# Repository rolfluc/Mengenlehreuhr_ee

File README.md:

# Mengenlehreuhr_ee
Project housing the electrical side of the Mengenlehreuhr project. Meant to be paired with the SW results.

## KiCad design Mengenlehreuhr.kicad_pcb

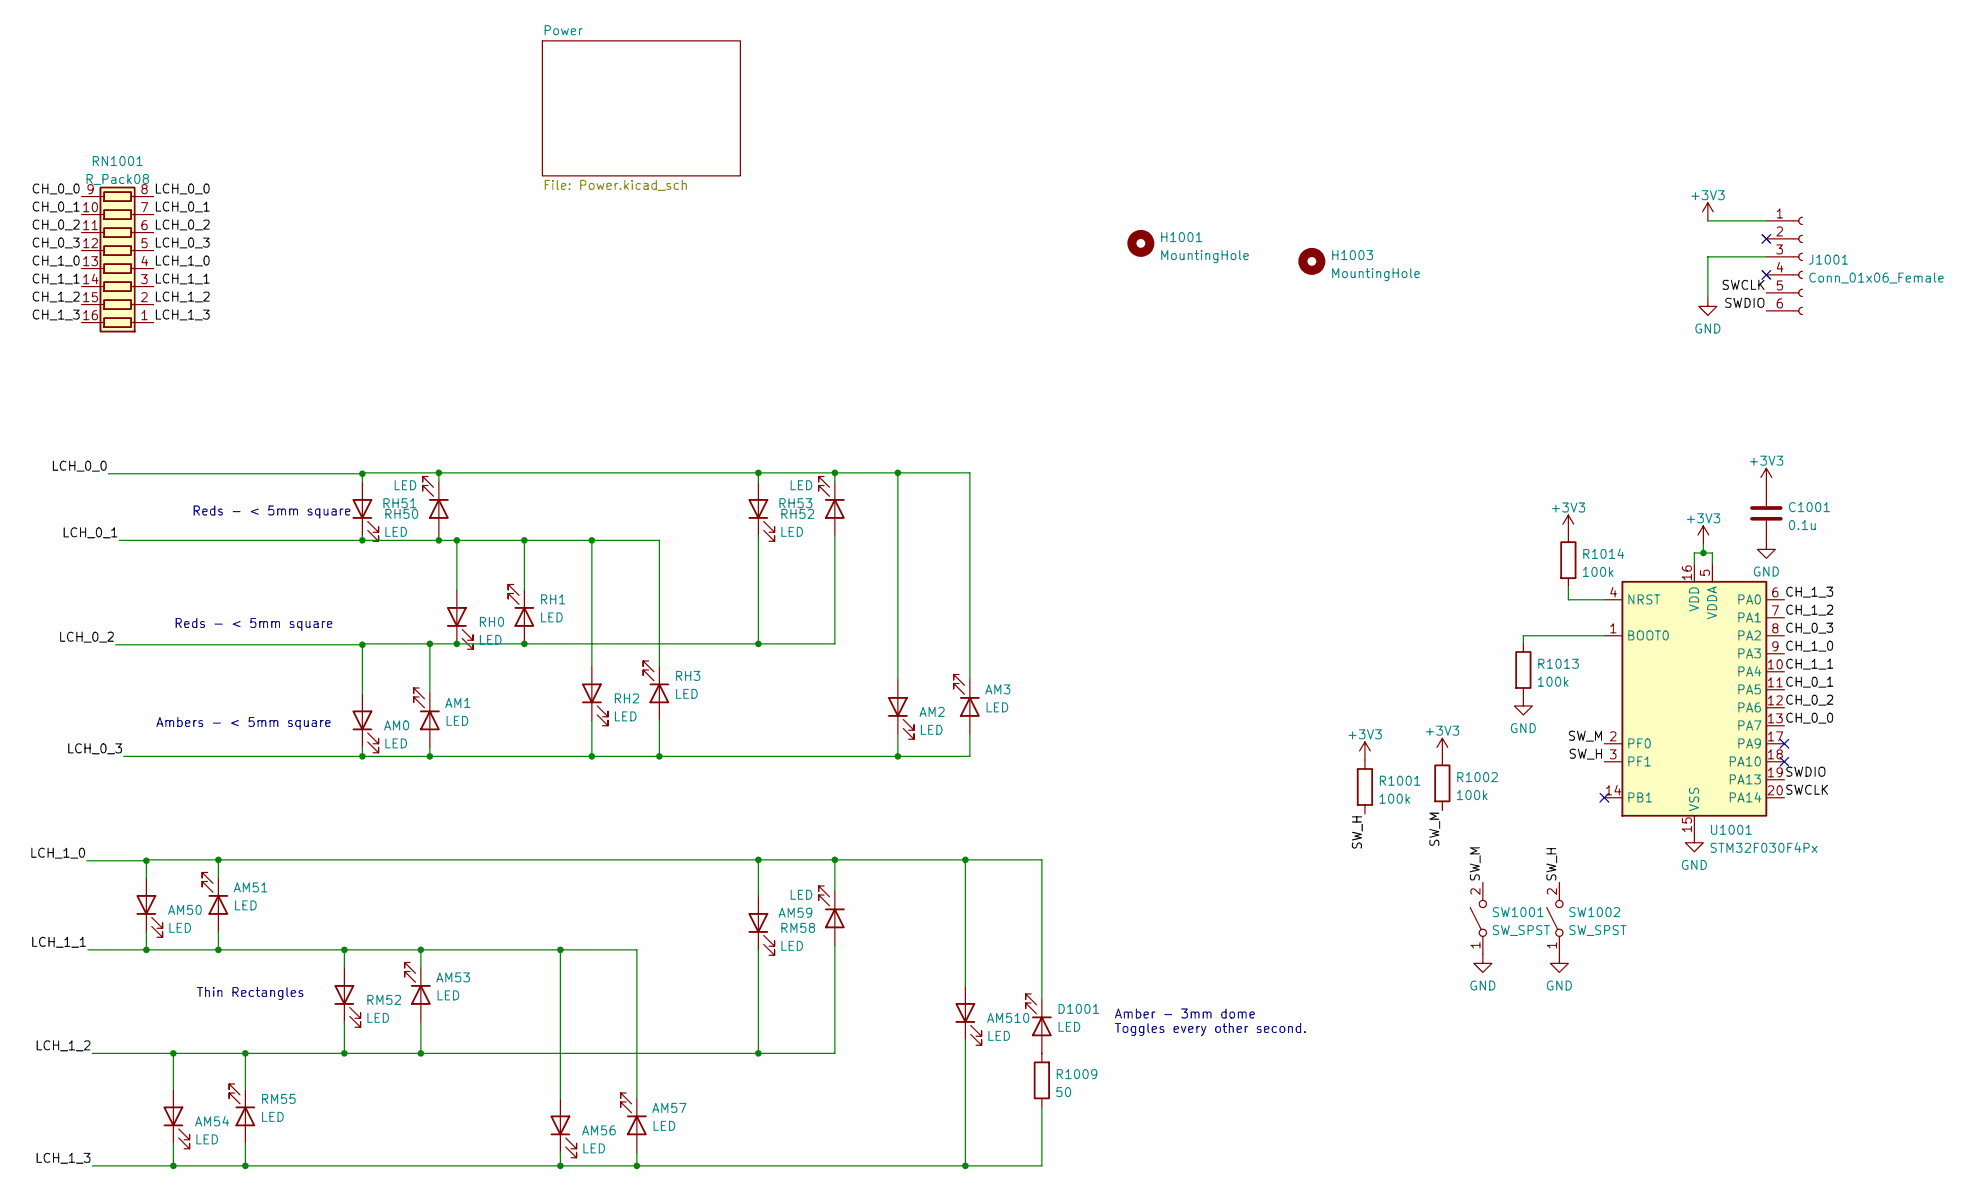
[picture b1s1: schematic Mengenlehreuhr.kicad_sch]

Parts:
AM0, AM1, AM2, AM3: LED; LED_1206_3216Metric
AM50, AM51, AM53, AM54, AM56, AM57, AM59, AM510: LED; LED_0603_1608Metric
C1001: 0.1u; C_0402_1005Metric
D1001: LED; LED_D3.0mm
H1001, H1003: MountingHole; MountingHole_3.2mm_M3
J1001: Conn_01x06_Female; Tag-Connect_TC2030-IDC-NL_2x03_P1.27mm_Vertical
R1001, R1002: 100k; R_0402_1005Metric_Pad0.72x0.64mm_HandSolder
R1009: 50; R_0402_1005Metric
R1013, R1014: 100k; R_0402_1005Metric
RH0, RH1, RH2, RH3, RH50, RH51, RH52, RH53: LED; LED_1206_3216Metric
RM52, RM55, RM58: LED; LED_0603_1608Metric
RN1001: R_Pack08; SOIC-16_3.9x9.9mm_P1.27mm
SW1001, SW1002: SW_SPST; SW_SPST_TL3305A
U1001: STM32F030F4Px; TSSOP-20_4.4x6.5mm_P0.65mm

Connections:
+3V3: C1001.1, J1001.1, R1001.1, R1002.1, R1014.1, U1001.5 (VDDA), U1001.16 (VDD); also elsewhere on the board
/CH_0_0: RN1001.9 (R8.2), U1001.13 (PA7)
/CH_0_1: RN1001.10 (R7.2), U1001.11 (PA5)
/CH_0_2: RN1001.11 (R6.2), U1001.12 (PA6)
/CH_0_3: RN1001.12 (R5.2), U1001.8 (PA2)
/CH_1_0: RN1001.13 (R4.2), U1001.9 (PA3)
/CH_1_1: RN1001.14 (R3.2), U1001.10 (PA4)
/CH_1_2: RN1001.15 (R2.2), U1001.7 (PA1)
/CH_1_3: RN1001.16 (R1.2), U1001.6 (PA0)
/LCH_0_0: AM2.2 (A), AM3.1 (K), RH50.2 (A), RH51.1 (K), RH52.2 (A), RH53.1 (K), RN1001.8 (R8.1)
/LCH_0_1: RH0.2 (A), RH1.1 (K), RH2.2 (A), RH3.1 (K), RH50.1 (K), RH51.2 (A), RN1001.7 (R7.1)
/LCH_0_2: AM0.2 (A), AM1.1 (K), RH0.1 (K), RH1.2 (A), RH52.1 (K), RH53.2 (A), RN1001.6 (R6.1)
/LCH_0_3: AM0.1 (K), AM1.2 (A), AM2.1 (K), AM3.2 (A), RH2.1 (K), RH3.2 (A), RN1001.5 (R5.1)
/LCH_1_0: AM50.2 (A), AM51.1 (K), AM59.1 (K), AM510.2 (A), D1001.1 (K), RM58.2 (A), RN1001.4 (R4.1)
/LCH_1_1: AM50.1 (K), AM51.2 (A), AM53.1 (K), AM56.2 (A), AM57.1 (K), RM52.2 (A), RN1001.3 (R3.1)
/LCH_1_2: AM53.2 (A), AM54.2 (A), AM59.2 (A), RM52.1 (K), RM55.1 (K), RM58.1 (K), RN1001.2 (R2.1)
/LCH_1_3: AM54.1 (K), AM56.1 (K), AM57.2 (A), AM510.1 (K), R1009.1, RM55.2 (A), RN1001.1 (R1.1)
/SWCLK: J1001.5, U1001.20 (PA14)
/SWDIO: J1001.6, U1001.19 (PA13)
/SW_H: R1001.2, SW1002.2 (B), U1001.3 (PF1)
/SW_M: R1002.2, SW1001.2 (B), U1001.2 (PF0)
GND: C1001.2, J1001.3, R1013.2, SW1001.1 (A), SW1002.1 (A), U1001.15 (VSS); also elsewhere on the board
unnamed: D1001.2 (A), R1009.2
unnamed: R1013.1, U1001.1 (BOOT0)
unnamed: R1014.2, U1001.4 (NRST)

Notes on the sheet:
Ambers - < 5mm square
Thin Rectangles
Amber - 3mm dome Toggles every other second.
Reds - < 5mm square

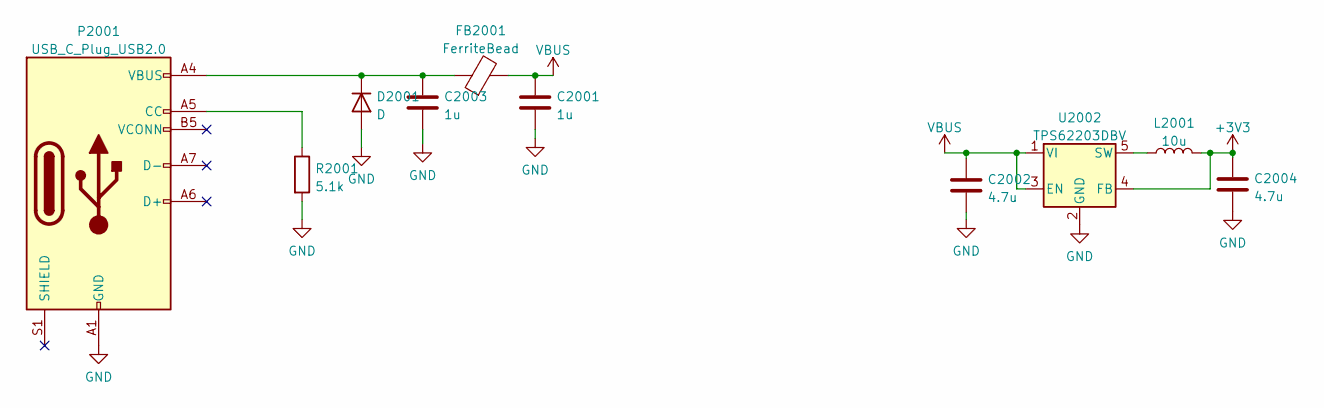
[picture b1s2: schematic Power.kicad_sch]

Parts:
C2001, C2003: 1u; C_0402_1005Metric
C2002, C2004: 4.7u; C_0603_1608Metric
D2001: D; D_0805_2012Metric_Pad1.15x1.40mm_HandSolder
FB2001: FerriteBead; R_0402_1005Metric_Pad0.72x0.64mm_HandSolder
L2001: 10u; L_1206_3216Metric
P2001: USB_C_Plug_USB2.0; USB_C_Receptacle_GCT_USB4085
R2001: 5.1k; R_0402_1005Metric
U2002: TPS62203DBV; SOT-23-5

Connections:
+3V3: C2004.1, L2001.2, U2002.4 (FB); also elsewhere on the board
GND: C2001.2, C2002.2, C2003.2, C2004.2, D2001.2 (A), P2001.A1 (GND), P2001.A12 (GND), P2001.B1 (GND), P2001.B12 (GND), R2001.2, U2002.2 (GND); also elsewhere on the board
unnamed 22: C2003.1, D2001.1 (K), FB2001.1, P2001.A4 (VBUS), P2001.A9 (VBUS), P2001.B4 (VBUS), P2001.B9 (VBUS); also elsewhere on the board
unnamed: L2001.1, U2002.5 (SW)
unnamed: P2001.A5 (CC), R2001.1
VBUS: C2001.1, C2002.1, FB2001.2, U2002.1 (VI), U2002.3 (EN)

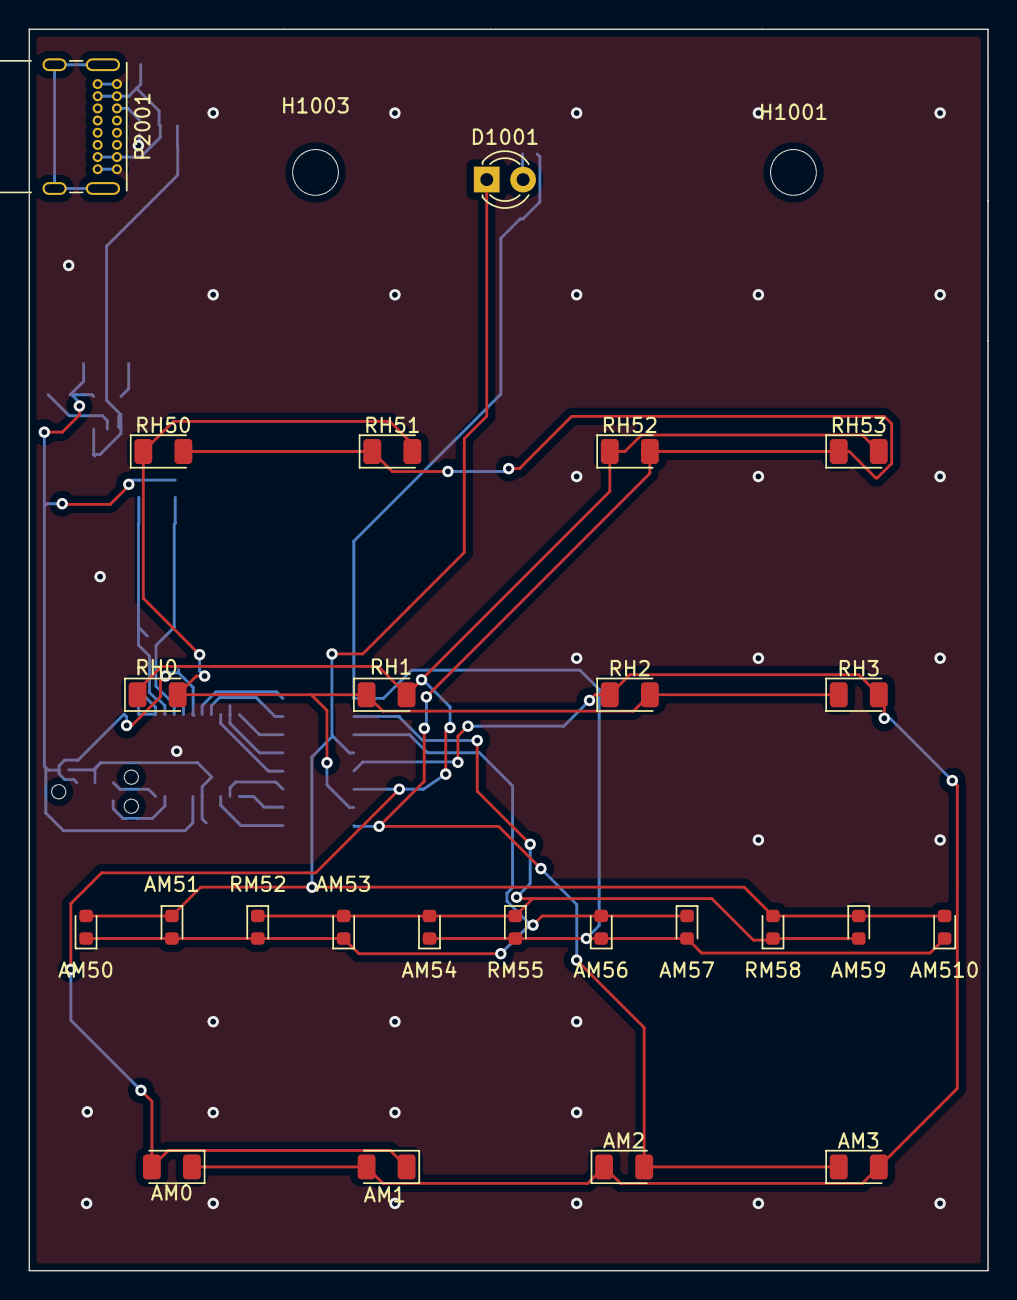
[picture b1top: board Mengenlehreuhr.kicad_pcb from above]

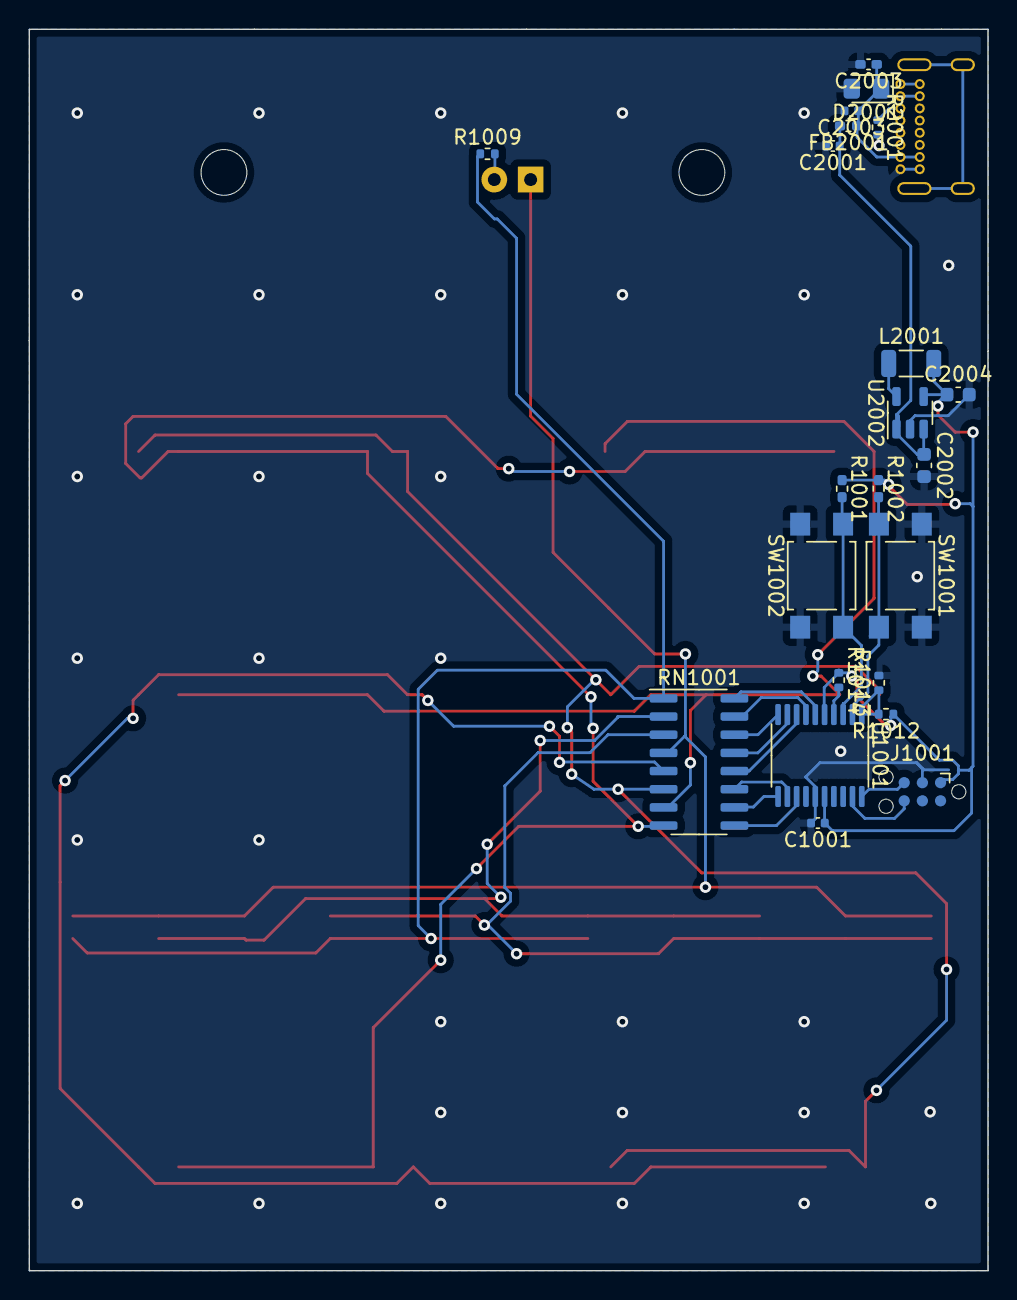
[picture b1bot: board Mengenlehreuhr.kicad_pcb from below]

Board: 2 copper layers, 67.0 x 86.8 mm, 49 parts (22 on the bottom side), 29 nets.

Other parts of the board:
C2003#2: 1u; C_0402_1005Metric_Pad0.74x0.62mm_HandSolder
R1012: 100k_np; R_0402_1005Metric

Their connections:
+3V3: R1012.1; also elsewhere on the board
GND: C2003#2.2; also elsewhere on the board
unnamed 22: C2003#2.1; also elsewhere on the board

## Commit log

2023-09-02 First and Last commit - EE Files
